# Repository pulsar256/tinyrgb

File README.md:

TinyRGB
=======

##Abstract

TinyRGB is a small learning project of mine. The goal is to replace / provide remote controlled drivers of
RGB strips by a small Bluetooth-Enabled controller and driver.

##Design Considerations
The board layout has been restricted to 5x5cm so you can get your PCBs produced for instance by Seeedstudio for
very little investment. The ATTiny4313 microcontroller has been chosen with the Arduino-Community in mind. While
this chip is not compatible with your Arduino-IDE per se, it is very closely related to it and should make it
a little bit more accessible. The HC-05 Bluetooth module used is one of the most popular ones across the
maker/hacker communities and can be sourced for few Dollar/Euro from eBay.

##Protocol Specification

The TinyRGB Firmware supports 4 basic modes:

- Random RGB Fade Mode
- RGB Flasher Mode
- HSL Fader Mode
- Fixed RGB Mode

The modes can be configured using a simple and compact serial protocol which makes some sacrifices
in order to maintain "human" compatibility while being designed to be remote controlled by a rich
GUI application.

The implementation supports the following commands sent via a serial modem link (8 9600 8n1 None):
```
"SRGB:RRRGGGBBB"      set R/G/B values, implicit change to mode 001 - fixed RGB/HSL.
"SW:WWW"              set white level (unsupported by the current hardware)
"SO:±RR±GG±BB"        set offset R/G/B values for RGB Fade Mode (+/-99)
"SM:RRRGGGBBB"        set maximum R/G/B values for RGB Fade Mode
"SHSL:HHHSSSLL"       set the H/S/L values. Pass -01 to ignore a value.
"SMD:MMM"             set mode:
                       001 - fixed RGB/HSL
                       002 - random RGB fader
                       003 - HSL fader
                       004 - RGB Flasher
"SD:DDD"              set delay for fade / flash modes.
"SAV:VVV"             enables (VVV > 0) or disables (VVV == 0) the eeprom autosave function.
"status"              get current RGB values and mode
"help"                help screen.
```

Setting HSL values does not put the controller into a fixed color mode. If you want to tweak partial HSL registers
while the colorcycling is active, you can pass a negative value to any color component to ignore it. For example
adjusting the saturation while not disturbing the hue position can be executed as: "SHSL:-01128-01"

If you want to implement a continuous color cycling or other effects on the controller side, disabling the eeprom
(via "SAV:000") is highly recommended to prevent the eeprom wearing. This mode is not persistent.

RGB offsets and maximum caps only apply to mode 002 (RGB Fader)

##Current Status
###Hardware

The hardware can be considered to be beta at best. Changes to be considered for a new HW revision:

- [ ] 7805 regulator needs to be Rotated by 180° to prevent issues with heatsink mounting
- [ ] Better decoupling
- [ ] Bump up the PCB size to 5x10cm to enable the hardware changes below.
- [ ] Use a 16MHz quartz instead of 20 to improve compatibility with standard UART baudrates.
- [ ] Hook up HC05 pin 34 to the AVR to enable the AT Mode.
- [ ] needs verification: hook up HC05 Reset line to the AVR to exit the AT mode. If powercycling is required, use a transitor to control the VCC line.
- [ ] Optional: status LEDS for the HC-05 module (pin 31, pin 32)
- [ ] Use 4  mosfets instead of the ULN2003 transistor array to drive loads > 1A per channel enabling the 4th white channel found on some RGB+W strips.
- [ ] TBD: Use the PCB as a heatsink for the 7805, alternatively put the regulator to one side of the PCB so it can be bend in a 90° angle and attach a dedicated heatsink "offboard".
- [ ] Use higher resistor values for the status and power leds to save ~15-20 mA

Please note, that the BT HC05 module will consume about 50mA current while in pairing mode and about 8mA
(according th the data sheet http://www.exp-tech.de/service/datasheet/HC-Serial-Bluetooth-Products.pdf)
while paired. This needs to be verified, the whole system will consume upto 45mA in idle (status LED lit)
and 70mA while paired.

###Firmware

The firmware controls the RGB channels via PWM and stores its last state in the eeprom to retain
its settings on a power cycle. See the protocol specification for further details on implemented
features and modes.

Open issues:

- [ ] Provide a unix makefile and integration with avrdude
- [ ] try to improve power consumption in pairing mode, 7805 regulator will be running quite hot otherwise.
- [ ] change the HC-05 BT Module name to TinyRGB on first boot. (hardware fix required)

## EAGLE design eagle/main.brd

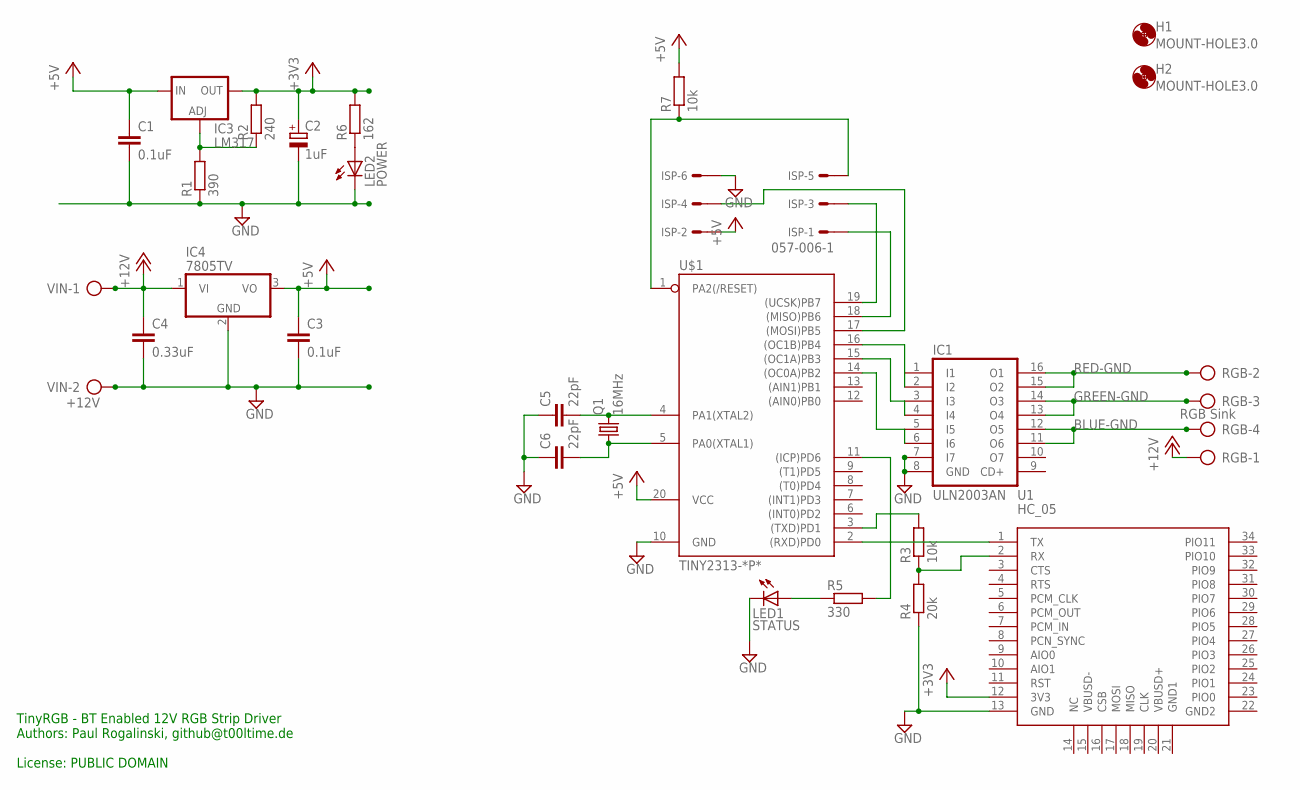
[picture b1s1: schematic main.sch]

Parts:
C1, C3: 0.1uF; C025-025X050
C2: 1uF; E2-5
C4: 0.33uF; C025_050-025X075
C5, C6: 22pF; C025-024X044
H1, H2: MOUNT-HOLE3.0; 3,0
IC1: ULN2003AN; DIL16
IC3: LM317; 317L
IC4: 7805TV; TO220V
ISP: 057-006-1
LED1: STATUS; LED3MM
LED2: POWER; LED3MM
Q1: 16MHz; HC49U-V
R1: 390; 0207/5V
R2: 240; 0207/5V
R3, R7: 10k; 0207/5V
R4: 20k; 0207/5V
R5: 330; 0207/5V
R6: 162; 0207/5V
RGB: RGB Sink; AK500/4
U1: HC_05; BLUETOOTH_SMD
U$1: TINY2313-*P*; DIL20
VIN: +12V; AK500/2

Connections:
+3V3: C2.+, IC3.2 (OUT), R2.2, R6.2, U1.12 (3V3)
+5V: C1.1, C3.1, IC3.3 (IN), IC4.3 (VO), ISP.2, R7.2, U$1.20 (VCC)
+12V: C4.1, IC4.1 (VI), RGB.1, VIN.1
BLUE-GND: IC1.11 (O6), IC1.12 (O5), RGB.4
GND: C1.2, C2.-, C3.2, C4.2, C5.1, C6.1, IC1.7 (I7), IC1.8 (GND), IC4.2 (GND), ISP.6, LED1.K (C), LED2.K (C), R1.1, R4.1, U1.13 (GND), U$1.10 (GND), VIN.2
GREEN-GND: IC1.13 (O4), IC1.14 (O3), RGB.3
unnamed: R3.2, U$1.3 ((TXD)PD1)
unnamed: U1.1 (TX), U$1.2 ((RXD)PD0)
unnamed: IC3.1 (ADJ), R1.2, R2.1
unnamed: IC1.1 (I1), IC1.2 (I2), U$1.16 ((OC1B)PB4)
unnamed: IC1.3 (I3), IC1.4 (I4), U$1.15 ((OC1A)PB3)
unnamed: IC1.5 (I5), IC1.6 (I6), U$1.14 ((OC0A)PB2)
unnamed: C5.2, Q1.2, U$1.4 (PA1(XTAL2))
unnamed: C6.2, Q1.1, U$1.5 (PA0(XTAL1))
unnamed: ISP.1, U$1.18 ((MISO)PB6)
unnamed: R3.1, R4.2, U1.2 (RX)
unnamed: ISP.3, U$1.19 ((UCSK)PB7)
unnamed: ISP.4, U$1.17 ((MOSI)PB5)
unnamed: ISP.5, R7.1, U$1.1 (PA2(/RESET))
unnamed: LED1.A, R5.1
unnamed: LED2.A, R6.1
unnamed: R5.2, U$1.11 ((ICP)PD6)
RED-GND: IC1.15 (O2), IC1.16 (O1), RGB.2

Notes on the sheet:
TinyRGB - BT Enabled 12V RGB Strip Driver Authors: Paul Rogalinski, github@t00ltime.de License: PUBLIC DOMAIN

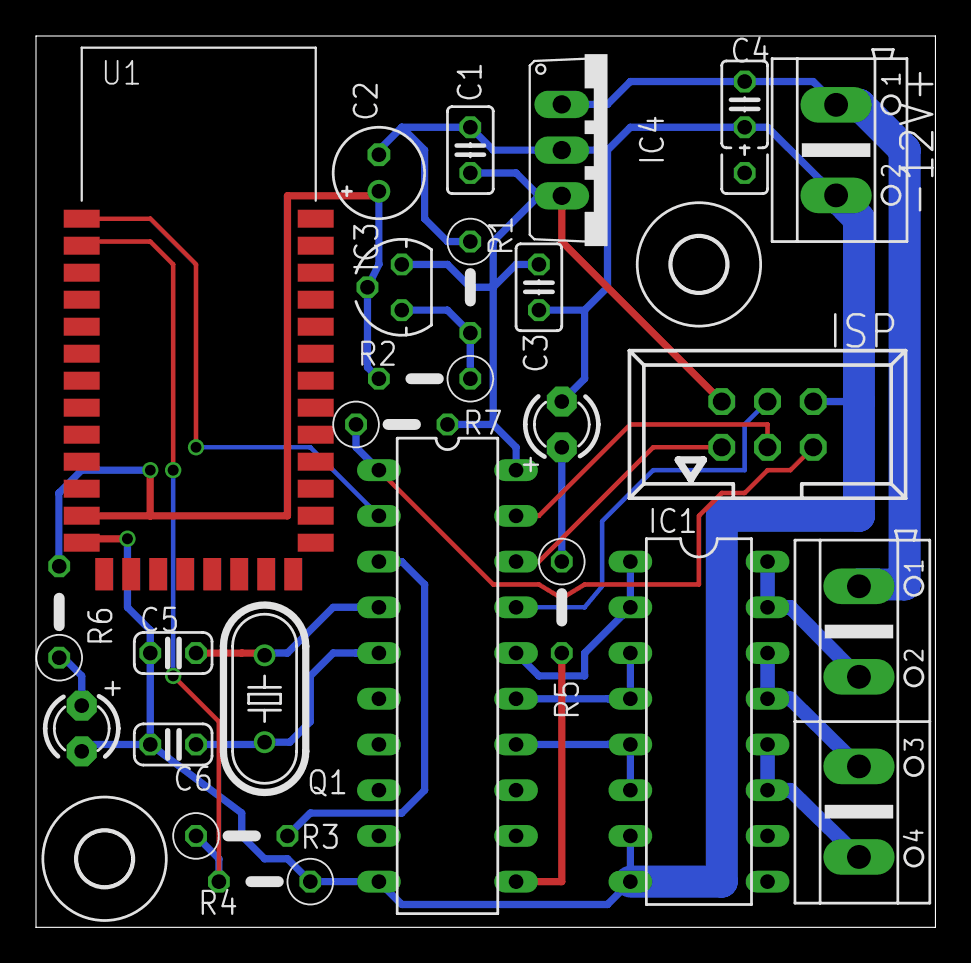
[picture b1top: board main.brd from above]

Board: 4 copper layers, 50.0 x 49.5 mm, 26 parts (0 on the bottom side), 23 nets.

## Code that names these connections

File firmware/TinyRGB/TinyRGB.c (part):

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* Pins:
*  2: RX  -> BT TX
*  3: TX  -> BT RX
* 11: PD6 -> Status LED
* 14: PB2 / OC0A -> Blue
* 15: PB3 / OC1A -> Green
* 16: PB4 / OC1B -> RED
*  9: PD5 / OC0B -> White (unsupported by the current hardware design)
\o/
*/
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
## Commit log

2013-10-01 initial import
2013-10-01 schematic image
2013-10-01 Update README.md
    Project description
2014-01-03 - added support for a dedicated white channel (not supported by the current hardware) - work in progress: command parser.
2014-01-03 Code cleanup & serial communication protocol
2014-01-03 Serial protocol / state retention
2014-01-03 documentation
2014-01-03 removed duplicate
2014-01-03 fixed some typos
2014-01-03 Various bugfixes in mRgb/oRgb handling.
2014-01-03 Minor help screen & protocol tweaks
2014-01-03 eeprom: autosave enable/disable, store white level
    + documentation comments and code cleanup
2014-01-03 Code Cosmetics
2014-01-03 Update TinyRGB.c
    autosaveEnabled was used to display it's state but was possibly not honoured when saving... possibly fixed now (no idea how to compile and test on mobile phone in github editor while being in the bat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
2014-01-03 Code cosmetics and minor optimizations.
    also added the fimrware.hex "binary"
2014-01-04 Code optimization & cosmetics
    - Removed dormant code
    - Fixed typos and formatting
    - completed documentation
    - Optimized for codesize
2014-01-04 Cosmetics
2014-01-04 Fixed HSV Fader (now HSL)
    - replaced the HSV implementation with a HSL,
    adapted http://tog.acm.org/resources/GraphicsGems/gems/HSLtoRGB.c
    - Color-Conversion uses references now
    - Updated documentation
2014-01-04 Bugfixes
2014-01-05 New Mode (RGB Flasher), Re-Ordered Modes.
2014-01-06 Slower transitions (x10)
    also made attempts to get into the command (AT) mode of the bt module.
    It turned out not to be possible using the current hardware revision.
2014-01-06 Updated TODOs for next HW Revision.
2016-07-11 migrated to atmel stuio 7, code cleanup
